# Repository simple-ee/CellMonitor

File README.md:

# CellMonitor
Support me on patreon :)
<a href="https://www.patreon.com/bePatron?u=28741071" data-patreon-widget-type="become-patron-button">Become a Patron!</a>

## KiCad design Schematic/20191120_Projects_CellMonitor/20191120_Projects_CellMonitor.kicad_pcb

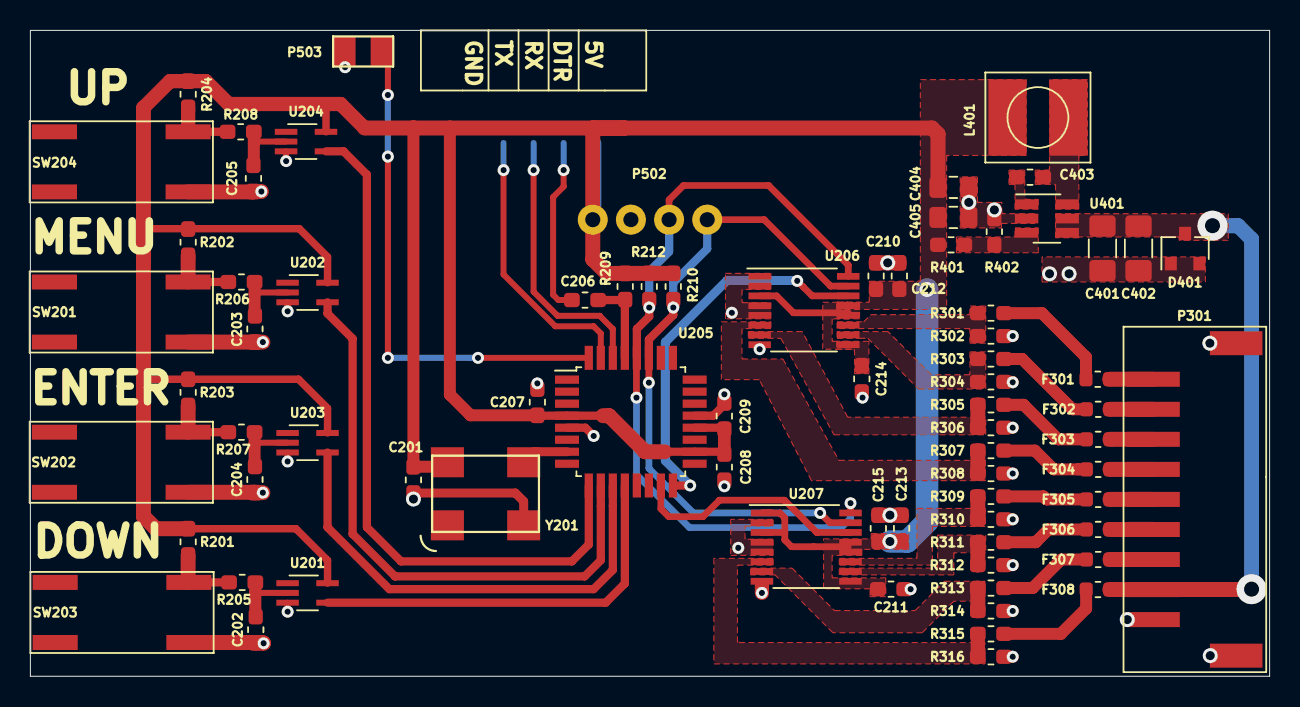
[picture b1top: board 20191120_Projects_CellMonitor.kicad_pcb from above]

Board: 2 copper layers, 82.5 x 43.0 mm, 76 parts (0 on the bottom side), 51 nets.

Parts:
C201, C202, C203, C204, C205, C206, C207, C208, C209, C210, C211, C212, C213, C214, C215, C403: CL10B104KB8NNNC; C_0603_Handsolder
C401, C402: UMK316BJ225KD-T; C_1206_Handsolder
C404, C405: GRT21BR61E226ME13L; C_0805_Handsolder
D401: DESD34VS2SO; SOT-23-3
F301, F302, F303, F304, F305, F306, F307, F308: 0686F1000-01; Fuse_0603_1608Metric
L401: MSS5131-103ML; MSS5131
P301: S9B-PH-SM4-TB(LF)(SN); S9B-PH-SM4-TB
P501: S5B-PH-SM4-TB(LF)(SN); S5B-PH-SM4-TB
P502: 096OLED; 096OLED_NOMOUNTS
P503: SMD_2POS
R201, R202, R203, R204, R205, R206, R207, R208, R209, R210, R212: ERA-3AEB103V; R_0603_Handsolder
R301: RC0603FR-0730KL; R_0603_Handsolder
R302, R304, R306, R308, R310, R312, R314, R316: CPF0603F100KC1; R_0603_Handsolder
R303: RR0816P-913-D; R_0603_Handsolder
R305: ERA-3AEB154V; R_0603_Handsolder
R307, R309: RT0603DRE07237KL; R_0603_Handsolder
R311: ERJ-3EKF3093V; R_0603_Handsolder
R313, R315: RC0603FR-07453KL; R_0603_Handsolder
R401, R402: RR0816P-2212-D-34C; R_0603_Handsolder
SW201, SW202, SW203, SW204: KSC721G
U201, U202, U203, U204: MC74HC1G04DFT1G; SOT-353_SC-70-5_Handsoldering
U205: ATMEGA328PB-AU; TQFP-32
U206, U207: ADS1119IPWR; TSSOP-16
U401: TPS560430YFDBVR; SOT-23-6
Y201: CB3-3I-16M0000; CB3

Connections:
+5V: C201.2, C207.1, C208.1, C209.1, C210.1, C211.1, C212.1, C213.1, C214.1, C215.1, C404.1, C405.1, L401.2, P501.5, P502.1, R201.2, R202.2, R203.2, R204.2, R209.1, R210.1, R212.1, R401.1, U201.5, U202.5, U203.5, U204.5, U205.4, U205.18, U205.20, U206.3, U206.9, U206.12, U206.13, U207.1, U207.3, U207.9, U207.12, U207.13, Y201.4
/sheet01/A_RX: P501.3, U205.30
/sheet01/A_TX: P501.2, U205.31
/sheet01/C0: R301.2, R302.1, U206.11
/sheet01/C1: R303.2, R304.1, U206.10
/sheet01/C2: R305.2, R306.1, U206.7
/sheet01/C3: R307.2, R308.1, U206.6
/sheet01/C4: R309.2, R310.1, U207.11
/sheet01/C5: R311.2, R312.1, U207.10
/sheet01/C6: R313.2, R314.1, U207.7
/sheet01/C7: R315.2, R316.1, U207.6
/sheet01/DOWN: U201.4, U205.12
/sheet01/DTR: C206.2, P501.4
/sheet01/ENTER: U203.4, U205.11
/sheet01/INT0: P503.1, U205.32
/sheet01/MENU: U202.4, U205.10
/sheet01/READ0: U205.16, U206.14
/sheet01/READ1: U205.15, U207.14
/sheet01/SCL: P502.3, R212.2, U205.28, U206.16, U207.16
/sheet01/SDA: P502.4, R210.2, U205.27, U206.15, U207.15
/sheet01/UP: U204.4, U205.9
/sheet01/XTAL1: U205.7, Y201.3
/sheet02/PIN: C401.1, C402.1, D401.3, F308.1, P301.2, U401.4, U401.5
/sheet02/cell0: F301.2, R301.1
/sheet02/cell1: F302.2, R303.1
/sheet02/cell2: F303.2, R305.1
/sheet02/cell3: F304.2, R307.1
/sheet02/cell4: F305.2, R309.1
/sheet02/cell5: F306.2, R311.1
/sheet02/cell6: F307.2, R313.1
/sheet02/cell7: F308.2, R315.1
GND: C201.1, C202.1, C203.1, C204.1, C205.1, C207.2, C208.2, C209.2, C210.2, C211.2, C212.2, C213.2, C214.2, C215.2, C401.2, C402.2, C404.2, C405.2, D401.1, D401.2, P301.1, P501.1, P502.2, P503.2, R302.2, R304.2, R306.2, R308.2, R310.2, R312.2, R314.2, R316.2, R402.2, SW201.1, SW202.1, SW203.1, SW204.1, U201.3, U202.3, U203.3, U204.3, U205.5, U205.21, U206.1, U206.2, U206.4, U206.5, U206.8, U207.2, U207.4, U207.5, U207.8, U401.2, Y201.2
unnamed: C202.2, R205.1, U201.2
unnamed: C203.2, R206.1, U202.2
unnamed: C204.2, R207.1, U203.2
unnamed: C205.2, R208.1, U204.2
unnamed: C206.1, R209.2, U205.29
unnamed: C403.1, L401.1, U401.6
unnamed: C403.2, U401.1
unnamed: F301.1, P301.9
unnamed: F302.1, P301.8
unnamed: F303.1, P301.7
unnamed: F304.1, P301.6
unnamed: F305.1, P301.5
unnamed: F306.1, P301.4
unnamed: F307.1, P301.3
unnamed: R201.1, R205.2, SW203.2
unnamed: R202.1, R206.2, SW201.2
unnamed: R203.1, R207.2, SW202.2
unnamed: R204.1, R208.2, SW204.2
unnamed: R401.2, R402.1, U401.3

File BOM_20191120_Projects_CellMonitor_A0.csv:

Item #,Description,References,Value,Quantity,P_Value,Manufacturer
1,"Ceramic Capacitor, 0.1uF, 50V, X7R, 0603",C201 C202 C203 C204 C205 C206 C207 C208 C209 C210 C211 C212 C213 C214 C215 C403,CL10B104KB8NNNC,16,0.1uF,Samsung Electro-Mechanics
2,"Ceramic Capacitor, 22uF, 25V, X5R, 0805",C404 C405,GRT21BR61E226ME13L,2,22uF,Murata Electronics North America
3,"Ceramic Capacitor, 2.2uF, 50V, X5R, 1206",C401 C402,UMK316BJ225KD-T,2,2.2uF,Taiyo Yuden
4,"TVS Diode, 34Vm, 43VCL, 36VBR, SOT-23-3",D401,DESD34VS2SO,1,34Vm,
5,"Fuse, 1A, 63VDC, slow blow, 0603",F301 F302 F303 F304 F305 F306 F307 F308,0686F1000-01,8,1A,Bel Fuse Inc
6,"Inductor, 10uH, 1.13A, 0.070R, MSS5131",L401,MSS5131-103ML,1,10uH,Coilcraft
7,"Display, 0.96 OLED, 128x64, DIYMALL, TH",P502,096OLED,1,128x64,DIYMALL
8,"Connector, 5POS, 2mm, JST Sales America Inc., SMD",P501,S5B-PH-SM4-TB(LF)(SN),1,5POS,JST Sales America Inc.
9,"Connector, 9POS, 2mm, JST Sales America Inc., SMD",P301,S9B-PH-SM4-TB(LF)(SN),1,9POS,JST Sales America Inc.
10,,P503,SMD_2POS,1,2POS,CUSTOM
11,"Resistor, 100k, 1%, 1/10W, 0603",R302 R304 R306 R308 R310 R312 R314 R316,CPF0603F100KC1,8,100k,TE Connectivity Passive Product
12,"Resistor, 10k, 0.1%, 1/10W, 0603",R201 R202 R203 R204 R205 R206 R207 R208 R209 R210 R212,ERA-3AEB103V,11,10k,Panasonic Electronic Components
13,"Resistor, 453k, 1%, 1/10W, 0603",R301 R303 R305 R307 R309 R311 R313 R315,RC0603FR-07453KL,8,453k,Yageo
14,"Resistor, 22.1k, 0.5%, 1/16W, 0603",R401 R402,RR0816P-2212-D-34C,2,*88.7k 22.1k,Susumu
15,"Switch, SPST-NO Tactile button, 0.05A @ 32VDC, SMD",SW201 SW202 SW203 SW204,KSC721G,4,SPST-NO,C&K
16,"ADC, 16-BIT, 2V- 5V5, 4 Single Ended / 2 Differential, TSSOP-16",U206 U207,ADS1119IPWR,2,16-BIT,Texas Instruments
17,"MCU, ATMEGA328PB-AU, 1V8-5V, TQFP-32",U205,ATMEGA328PB-AU,1,MCU,Atmega
18,"Logic Gate, Inverting Gate, 2V-6V, SC-70-5",U201 U202 U203 U204,MC74HC1G04DFT1G,4,Inverter Gate,ON Semiconductor
19,"IC, Buck Converter, ADJ 0.6A Peak, 2.1MHz, SOT-23-6",U401,TPS560430YFDBVR,1,TPS560430YFDBVR,Texas Instrument
20,"Crystal, 16MHz, HCMOS/TTL,4_SMD",Y201,CB3-3I-16M0000,1,16MHz,CTS-Frequency Controls
